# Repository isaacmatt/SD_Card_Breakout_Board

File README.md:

# microSD Card Breakout (SPI, 3.3 V)

A minimal microSD card breakout board for 3.3 V microcontrollers, exposing the card over a 1-bit SPI interface on a 0.1" header. Designed as a hands-on KiCad project with a clean, manufacturable layout.

> **Status:** Schematic and PCB layout complete. ERC and DRC clean (0 violations, 0 unconnected). **Not yet fabricated or tested** — this is a design-stage project. Footprint assignment, layout, and manufacturing files are done; the board has not been ordered, assembled, or brought up.

---

## Overview

This is a passive breakout: it routes a microSD connector to a pin header with the minimum support circuitry required for reliable operation, and nothing else. No onboard microcontroller, voltage regulator, level shifter, or USB. You supply 3.3 V from a host, jumper the SPI lines across, and talk to the card using a standard SD library on the host side.

The design deliberately targets the common denominator across 3.3 V hosts:  **SPI 1-bit mode** . SDIO/4-bit is intentionally out of scope.

## Features

* microSD (TF) push-push connector with spring eject
* SPI 1-bit interface broken out to a 1×8 0.1" header
* Pull-ups on all data lines per the SD specification
* Local decoupling (100 nF + 1 µF) at the connector's VDD pin
* 2-layer board with ground pours on both layers, via-stitched
* All passives 0603 (hand-solder friendly); designed for low-cost fab + assembly

## Specifications

| Property               | Value                                                    |
| ---------------------- | -------------------------------------------------------- |
| Interface              | SPI, 1-bit                                               |
| Logic / supply voltage | 3.3 V only (**not 5 V tolerant** )                 |
| Layers                 | 2 (signals on top, GND pours both layers)                |
| Connector              | SHOU HAN TF PUSH, push-push, 8 contacts + grounded shell |
| Connector LCSC P/N     | C393941                                                  |
| Card detection         | Firmware (no hardware detect switch — see below)        |
| EDA tool               | KiCad 10                                                 |

## Supported hosts

| Host                         | Supported         | Notes                                                                                                                                     |
| ---------------------------- | ----------------- | ----------------------------------------------------------------------------------------------------------------------------------------- |
| Raspberry Pi Pico W (RP2040) | ✅ Direct         | 3.3 V SPI host                                                                                                                            |
| nRF52840                     | ✅ Direct         | 3.3 V SPI host                                                                                                                            |
| Arduino Uno (ATmega328P)     | ⚠️ Not directly | 5 V logic — its SPI outputs would overdrive a 3.3 V card. Requires an external level shifter on SCK/MOSI/CS. Not included on this board. |

microSD cards operate at 2.7–3.6 V and are not 5 V tolerant. Any 5 V-logic host requires level shifting on the host-driven lines (SCK, MOSI, CS). MISO returns 3.3 V, which a 5 V AVR reads as a valid logic high, so only the outbound lines need shifting.

## Pinout

### microSD contact → SPI mapping

The microSD pinout is standardized. In SPI mode:

| Contact | Card name | SPI role       | On-board support          |
| ------- | --------- | -------------- | ------------------------- |
| 1       | DAT2      | unused         | 10 kΩ pull-up            |
| 2       | CD/DAT3   | **CS**   | 10 kΩ pull-up            |
| 3       | CMD       | **MOSI** | 10 kΩ pull-up            |
| 4       | VDD       | power          | 100 nF + 1 µF decoupling |
| 5       | CLK       | **SCK**  | —                        |
| 6       | VSS       | ground         | —                        |
| 7       | DAT0      | **MISO** | 10 kΩ pull-up            |
| 8       | DAT1      | unused         | 10 kΩ pull-up            |
| shell   | shield    | —             | tied to GND               |

DAT1 and DAT2 are unused in SPI mode but are pulled high so the card does not float into an undefined state at power-up.

### J2 header (1×8, 2.54 mm)

| Pin | Signal |
| --- | ------ |
| 1   | 3V3    |
| 2   | GND    |
| 3   | CS     |
| 4   | SCK    |
| 5   | MOSI   |
| 6   | MISO   |
| 7   | GND    |
| 8   | GND    |

The header order was chosen to keep board routing clean; the two extra grounds improve the jumper-wire return path.

## Card detection

The chosen connector has **no mechanical card-detect switch** — only the 8 SD contacts and a grounded shell. Card presence is therefore detected in  **firmware** : attempt to initialize the card over SPI, and if it responds, a card is present. This is standard practice for SD breakouts and removes a dependency on an underdocumented mechanical feature.

## Bill of Materials

| Ref | Value             | Package     | Notes                            |
| --- | ----------------- | ----------- | -------------------------------- |
| J1  | microSD connector | SMD         | SHOU HAN TF PUSH, LCSC C393941   |
| J2  | 1×8 header       | 2.54 mm THT | Hand-soldered after SMT assembly |
| C1  | 100 nF            | 0603        | Decoupling at VDD                |
| C2  | 1 µF             | 0603        | Bulk decoupling at VDD           |
| R1  | 10 kΩ            | 0603        | CS pull-up                       |
| R2  | 10 kΩ            | 0603        | MOSI pull-up                     |
| R3  | 10 kΩ            | 0603        | MISO pull-up                     |
| R4  | 10 kΩ            | 0603        | DAT1 pull-up                     |
| R5  | 10 kΩ            | 0603        | DAT2 pull-up                     |

## Design decisions & rationale

* **3.3 V-only, passive breakout.** Keeps the board simple and lets it work with any 3.3 V SPI host. Level shifting is treated as a host-side concern, not baked in.
* **SPI 1-bit mode.** The common denominator across target hosts; also simplifies the breakout to CS/SCK/MOSI/MISO + power.
* **Pull-ups on all data lines.** Per the SD physical-layer specification, including the unused DAT1/DAT2 so they don't float; CS is pulled high so it idles correctly.
* **Decoupling placed at the connector's VDD pin.** SD cards have real current inrush; the 100 nF + 1 µF sit immediately at the power pin where they're effective.
* **Connector selected for availability.** An active, in-stock, JLCPCB-assemblable part was prioritized over a "nicer" datasheet on an out-of-stock alternative — a manufacturability-driven choice.
* **Firmware card detection.** Chosen over relying on a hardware switch the connector doesn't have.
* **Dual-layer GND pour, via-stitched.** Grounds the connector shield, provides a low-impedance return, and ties both planes together.

## Manufacturing notes

Intended fab/assembly flow (JLCPCB):

1. Order bare PCBs + **economic SMT assembly** for the connector and 0603 passives.
2. Leave the **through-hole header (J2) off** the assembly and hand-solder it afterward — it's the easiest part and avoids THT assembly fees.
3. At the assembly stage, verify the connector's **pad-1 orientation** in the placement preview — connector rotation is the most common first-time assembly mistake.

The pull-up resistors and caps are all 0603 and the only THT part is the header, so the board is straightforward to assemble either by machine or by hand.

## Not included / limitations

* No level shifting — 3.3 V hosts only.
* No ESD protection — see roadmap.
* No mounting holes are electrically connected (the connector's holes are mechanical/NPTH).
* Untested; no firmware/driver provided. Use a standard SPI SD library on the host (e.g. Arduino `SD`/`SdFat`, CircuitPython `adafruit_sdcard`, or the RP2040/nRF SDKs).

## Roadmap (v2 ideas)

* Add a low-capacitance ESD/TVS array at the connector contacts (e.g. `USBLC6-2SC6` or a multi-channel low-cap array), placed before the pull-ups. Low capacitance matters so SPI edges aren't distorted.
* Optional level-shifted variant (e.g. `74LVC125` buffer + 3.3 V LDO) to support 5 V hosts like the Arduino Uno directly.
* Silkscreen the full header pinout next to J2 for at-a-glance jumpering.

## Repository structure

```
.
├── microSD_breakout.kicad_pro     # KiCad project
├── microSD_breakout.kicad_sch     # Schematic
├── microSD_breakout.kicad_pcb     # PCB layout
├── easyeda2kicad.pretty/          # Imported connector footprint
├── easyeda2kicad.kicad_sym        # Imported connector symbol
├── fab/                           # Gerbers, BOM, CPL (when generated)
├── docs/                          # Schematic / PCB / 3D renders
└── README.md
```

## Opening this project

The connector's symbol and footprint are **bundled in this repository** (`easyeda2kicad.pretty/`, `easyeda2kicad.kicad_sym`) so the project opens without external dependencies. The library tables reference them with the project-relative path variable `${KIPRJMOD}`, so the paths resolve correctly on any machine after cloning.

If KiCad reports a missing footprint or symbol after cloning, check that the footprint and symbol library tables point to the in-repo copies (Preferences → Manage Footprint/Symbol Libraries) using `${KIPRJMOD}/easyeda2kicad.pretty` and `${KIPRJMOD}/easyeda2kicad.kicad_sym`.

### Regenerating the connector footprint

The J1 footprint was imported from LCSC using [easyeda2kicad](https://github.com/uPesy/easyeda2kicad.py). To regenerate it from scratch:

```bash
pip install easyeda2kicad
easyeda2kicad --full --lcsc_id C393941
```

Then add the generated `easyeda2kicad.pretty` and `easyeda2kicad.kicad_sym` to your KiCad library tables. Using the EasyEDA/LCSC library this way ensures the footprint geometry matches JLCPCB's pick-and-place data for assembly.

## Wiring example

Connect the J2 header to your host's SPI pins. The exact host GPIO numbers depend on your board — fill in your host's SPI bus:

| J2 pin | Signal | → Host                      |
| ------ | ------ | ---------------------------- |
| 1      | 3V3    | 3.3 V                        |
| 2      | GND    | GND                          |
| 3      | CS     | any GPIO used as chip-select |
| 4      | SCK    | SPI clock                    |
| 5      | MOSI   | SPI MOSI / TX                |
| 6      | MISO   | SPI MISO / RX                |
| 7      | GND    | GND                          |
| 8      | GND    | GND                          |

## License

MIT — choose and add a `LICENSE` file. MIT is a common default for open hardware projects; adapt as you prefer.

## Author

**isaac-m** ([@isaacmatt](https://github.com/isaacmatt))

---

*Built in KiCad as a from-scratch PCB design exercise: connector selection and lifecycle/stock checking, third-party footprint import and verification, schematic capture, layout, ground-plane routing, and manufacturing-file preparation.*

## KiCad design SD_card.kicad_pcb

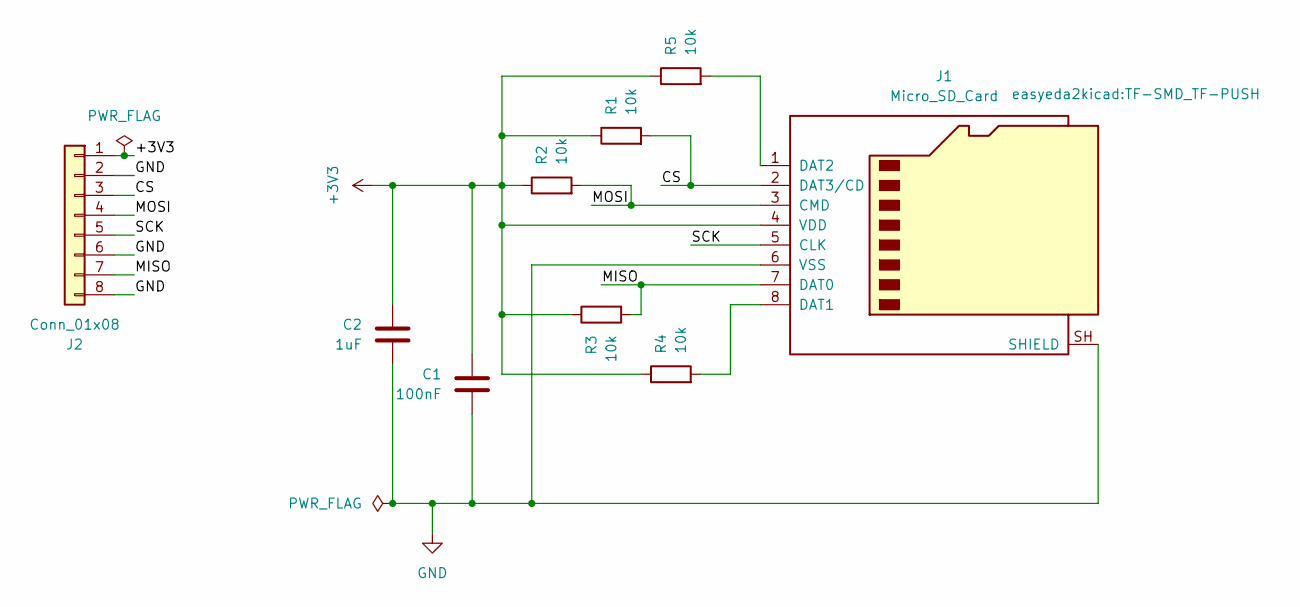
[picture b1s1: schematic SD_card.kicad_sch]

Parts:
C1: 100nF; C_0603_1608Metric
C2: 1uF; C_0603_1608Metric
J1: Micro_SD_Card; TF-SMD_TF-PUSH
J2: Conn_01x08; PinHeader_1x08_P2.54mm_Vertical
R1, R2, R3, R4, R5: 10k; R_0603_1608Metric

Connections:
+3V3: C1.1, C2.1, J1.4 (VDD), J2.1, R1.1, R2.1, R3.1, R4.1, R5.1
/CS: J1.2 (DAT3/CD), J2.3, R1.2
/MISO: J1.7 (DAT0), J2.7, R3.2
/MOSI: J1.3 (CMD), J2.4, R2.2
/SCK: J1.5 (CLK), J2.5
GND: C1.2, C2.2, J1.6 (VSS), J1.SH (SHIELD), J2.2, J2.6, J2.8
unnamed: J1.8 (DAT1), R4.2
unnamed: J1.1 (DAT2), R5.2

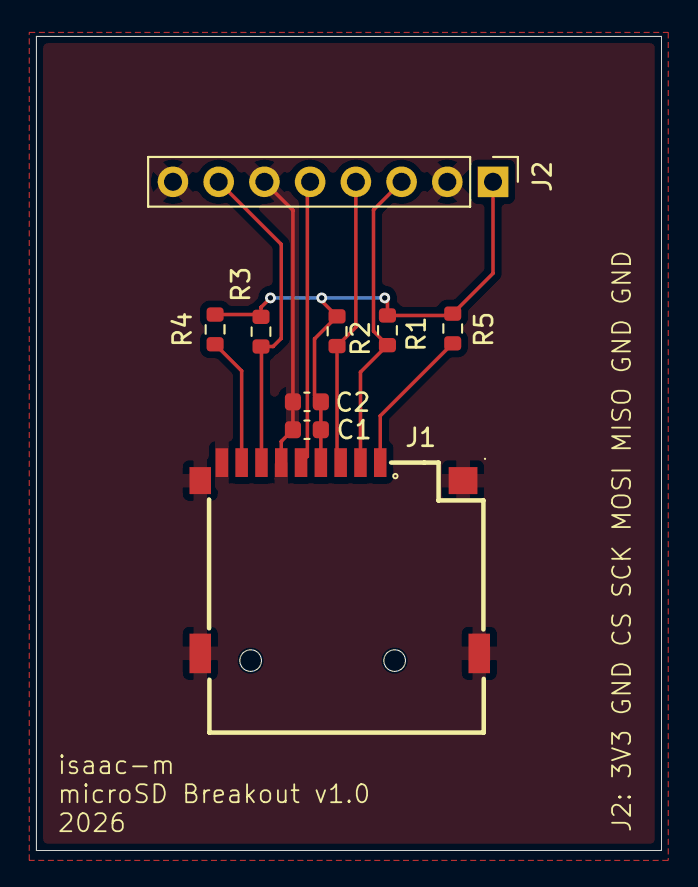
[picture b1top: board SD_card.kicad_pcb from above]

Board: 2 copper layers, 34.7 x 45.2 mm, 9 parts (0 on the bottom side), 8 nets.

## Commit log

2026-06-12 Initial KiCad project setup
    Add schematic and PCB project files, README, CERN-OHL-P-2.0 license, and KiCad gitignore rules.
2026-06-16 Complete PCB layout, DRC clean
    Routed all signals on F.Cu, GND pours on both layers with
    stitching vias. Fixed imported connector footprint (courtyard,
    NPTH holes, shell-tab naming). Added silkscreen labeling.
    Ready for fab output generation.
2026-06-16 Add detailed README for microSD breakout
    Replace the minimal README with a comprehensive project document covering status, overview, features, specifications, supported hosts, pinout, BOM, design rationale, manufacturing notes, limitations,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
